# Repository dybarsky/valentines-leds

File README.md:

## HEART LEDs Valentine's day gift.
An Open Source & Open Hardware project.  

_Demo gif (loads a bit long)_ 👇  

## Parts
The core of this project is `MSP430G2553` mictrocontroller by Texas Instruments and two `SN74HC595N` 8-bit shift registers. Each 8-bit shift register controls 8 3mm red LEDs. Also resistors, capacitors, slide switch, tacticle button, DIP sockets, Li-ion akku 3.7V, a JST connector.  

Check schematics below to get values for resistors and capacitors.  

Here are all used components 👇  

And this is how assembly looks like 👇  

## Schematic
I used KiCad to design hardware. Source files are located in `pcb` folder.  
This is a schematic diagram 👇

## PCB Design
KiCad project fies for PCB as well as Gerber files for PCB production are also located in `pcb` fodler.  
This is a PCB design 👇  

With highlighted nets 👇  

## Firmware
Firmware for this project was written in pure `C`, operating with IC registers directly (without platformio or any other ports of arduino libraries). It requires some deeper knowledge of MSP430G2553 datasheet and hardware communication protocols, but drastically reduces binary size. It's only 14 KB!  

There are 6 different patterns of LEDs blinking. They are store in 2 dimensional arrays of bytes.  
Timer intrruptions are configured to be called every 0.1 second. IC goes over array and sends data to 8-bit shift register. Communication between the microcontroller and 8-bit shift registers is done via `SPI` protocol. When IC is not busy, it goes to low power mode.

## Demo
https://www.youtube.com/watch?v=liG8lNvPkbY

## Instrucitons 
https://www.instructables.com/Electronic-Heart-Valentines-Day-Gift/

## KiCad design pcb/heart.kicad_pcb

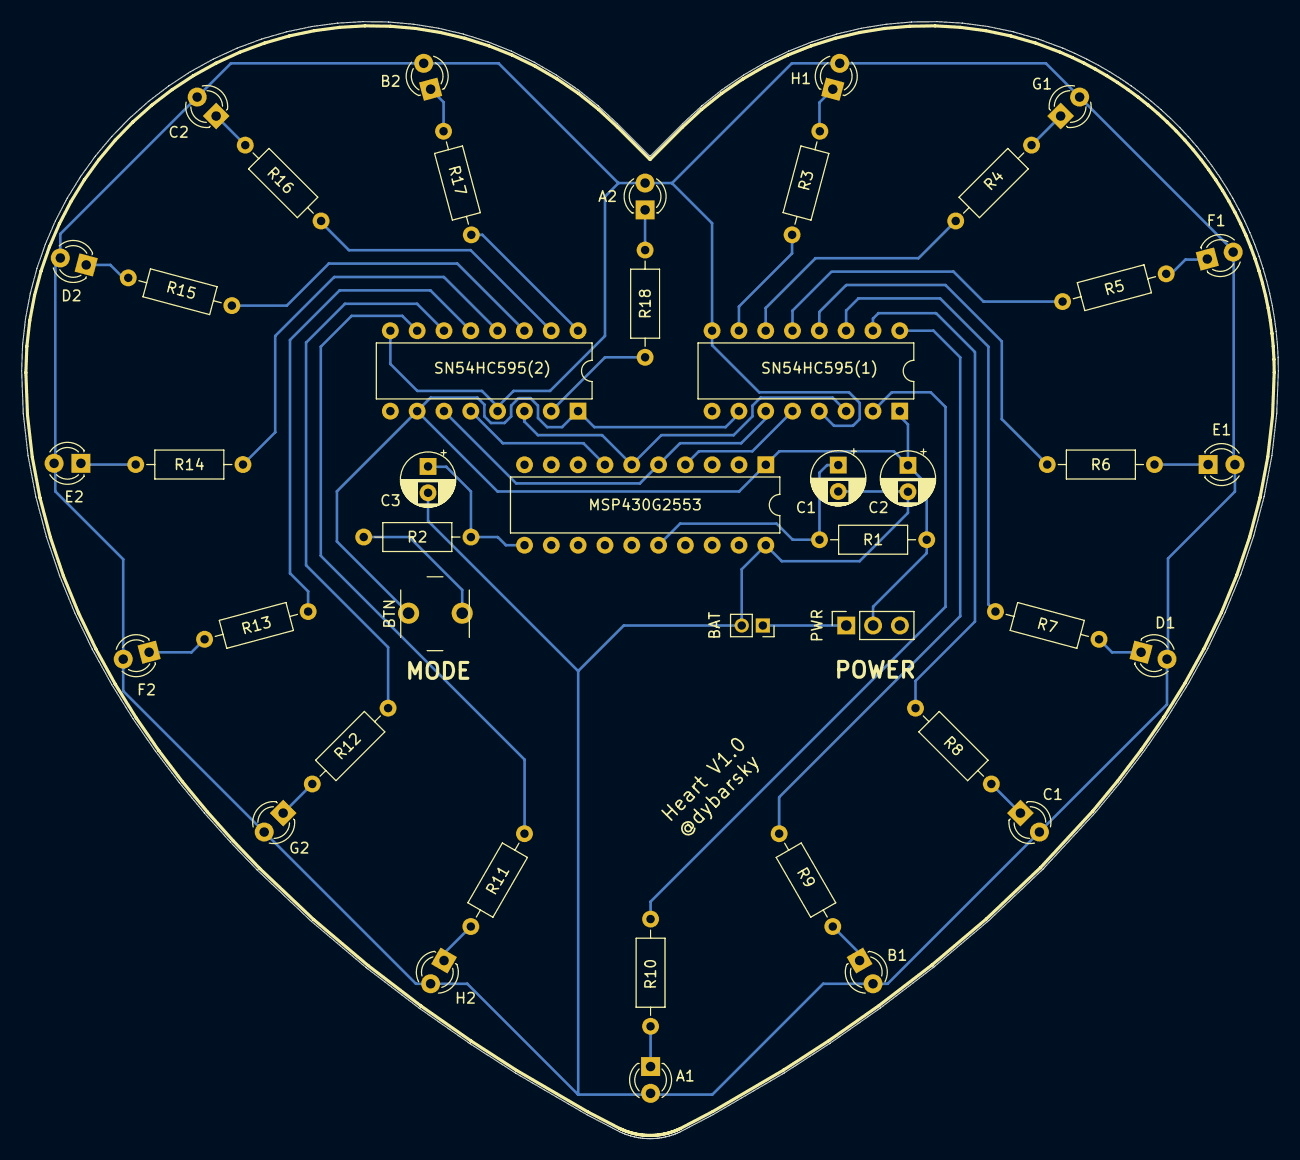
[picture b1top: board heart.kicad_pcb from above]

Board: 2 copper layers, 119.1 x 105.8 mm, 43 parts (0 on the bottom side), 9 nets.

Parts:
A1, A2: LED_D3.0mm
B1, B2: LED_D3.0mm
BAT: PinSocket_1x02_P2.00mm_Vertical
BTN: SW_PUSH_6mm_H5mm
C1, C2#2: LED_D3.0mm
C1#2, C2, C3: CP_Radial_D5.0mm_P2.50mm
D1, D2: LED_D3.0mm
E1, E2: LED_D3.0mm
F1, F2: LED_D3.0mm
G1, G2: LED_D3.0mm
H1, H2: LED_D3.0mm
MSP430G2553: DIP-20_W7.62mm
PWR: PinSocket_1x03_P2.54mm_Vertical
R1, R2, R3, R4, R5, R6, R7, R8, R9, R10, R11, R12, R13, R14, R15, R16, R17, R18: R_Axial_DIN0207_L6.3mm_D2.5mm_P10.16mm_Horizontal
SN54HC595(1), SN54HC595(2): DIP-16_W7.62mm

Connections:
BTN: C3.1, MSP430G2553.11, R2.1
CLK: MSP430G2553.5, SN54HC595(1).11, SN54HC595(2).11
DAT: MSP430G2553.6, SN54HC595(1).14, SN54HC595(2).14
GND: A1.2, A2.2, B1.2, B2.2, BAT.2, C1.2, C1#2.2, C2.2, C2#2.2, C3.2, D1.2, D2.2, E1.2, E2.2, F1.2, F2.2, G1.2, G2.2, H1.2, H2.2, MSP430G2553.20, SN54HC595(1).8, SN54HC595(1).13, SN54HC595(2).8, SN54HC595(2).13
LED: A1.1, A2.1, B1.1, B2.1, C1.1, C2#2.1, D1.1, D2.1, E1.1, E2.1, F1.1, F2.1, G1.1, G2.1, H1.1, H2.1, R3.1, R3.2, R4.1, R4.2, R5.1, R5.2, R6.1, R6.2, R7.1, R7.2, R8.1, R8.2, R9.1, R9.2, R10.1, R10.2, R11.1, R11.2, R12.1, R12.2, R13.1, R13.2, R14.1, R14.2, R15.1, R15.2, R16.1, R16.2, R17.1, R17.2, R18.1, R18.2, SN54HC595(1).1, SN54HC595(1).2, SN54HC595(1).3, SN54HC595(1).4, SN54HC595(1).5, SN54HC595(1).6, SN54HC595(1).7, SN54HC595(1).15, SN54HC595(2).1, SN54HC595(2).2, SN54HC595(2).3, SN54HC595(2).4, SN54HC595(2).5, SN54HC595(2).6, SN54HC595(2).7, SN54HC595(2).15
LTCH1: MSP430G2553.4, SN54HC595(1).12
LTCH2: MSP430G2553.7, SN54HC595(2).12
RST: C1#2.1, MSP430G2553.16, R1.1
VCC: BAT.1, BTN.1, BTN.2, C2.1, MSP430G2553.1, PWR.1, PWR.2, R1.2, R2.2, SN54HC595(1).10, SN54HC595(1).16, SN54HC595(2).10, SN54HC595(2).16

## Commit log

2025-02-05 Add gitignore
2025-02-05 Add timer control
2025-02-05 Add button control
2025-02-05 Add 8bit shift control
2025-02-05 Add main.c
2025-02-05 Add makefile
2025-02-05 Add schematics
2025-02-11 Add pattern.c
2025-02-11 Fix button.c
2025-02-11 Use patterns in main.c
2025-02-11 Fix shift.c
2025-02-11 Add more pattern
2025-02-12 Different sizes of pattern arrays
2025-02-12 Add beating pattern
2025-02-12 Add cheasing pattern
2025-02-12 Move pcb files one folder up
2025-02-13 Fix patterns
2025-02-14 Remove name from silkscreen
2025-02-14 Add version and author to silkscreen
2025-02-14 Add media files
2025-02-14 Add licence files
2025-02-14 Add demo media
2025-02-15 Introduce struct in firmware
2025-02-16 Update gerber files
2025-02-24 Update pcb design
2025-02-24 Update gitignore
2025-02-24 Add ifdef to headers
2025-02-24 Add github actions
2025-02-24 Add dockerfile
